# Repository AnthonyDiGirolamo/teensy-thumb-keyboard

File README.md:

# teensy-thumb-keyboard
Handheld tactile switch keyboard for Teensy 3.2 compatible boards.

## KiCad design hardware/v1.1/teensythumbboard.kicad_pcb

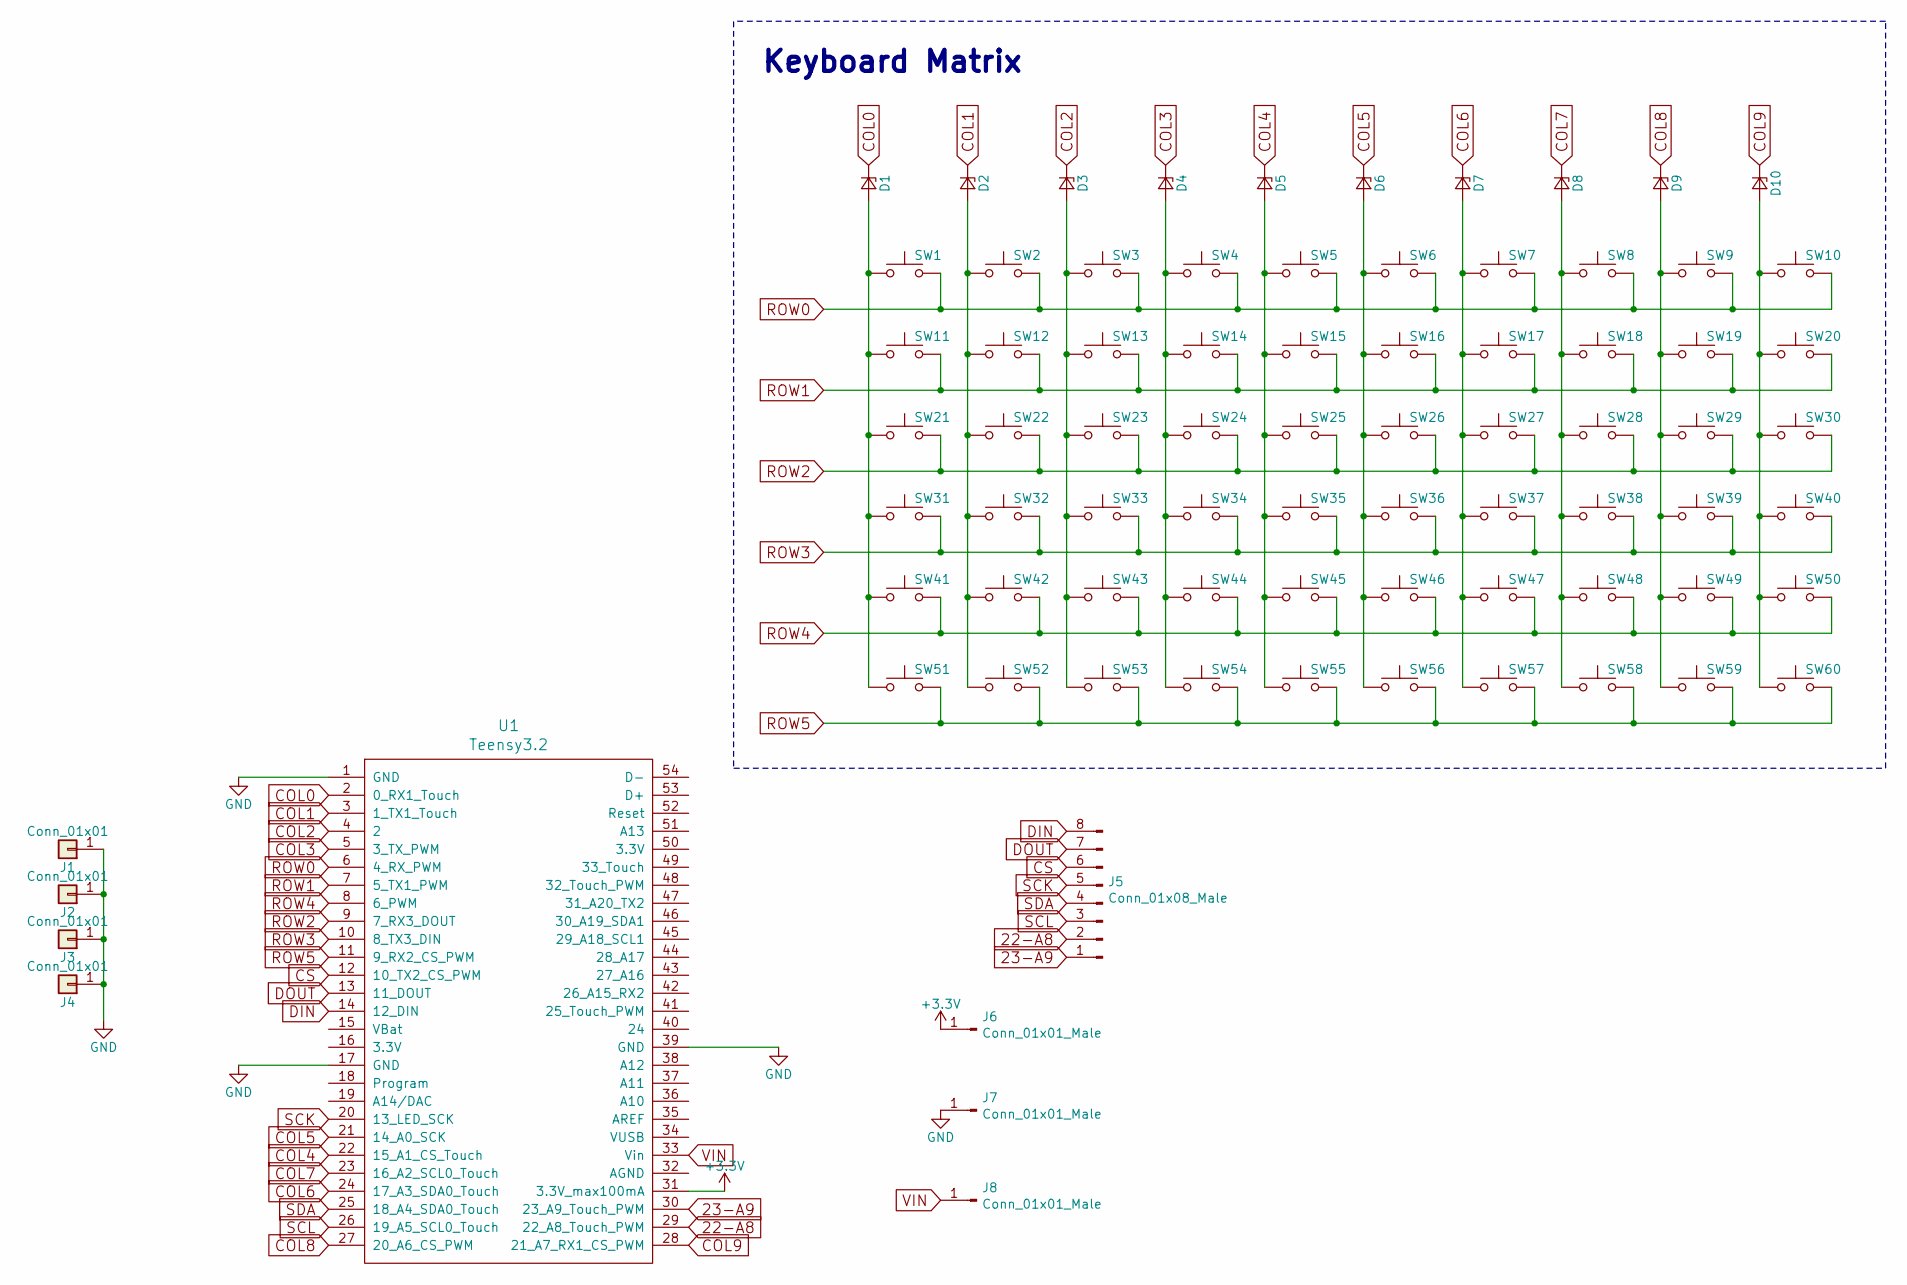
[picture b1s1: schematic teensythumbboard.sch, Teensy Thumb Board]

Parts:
D1, D2, D3, D4, D5, D6, D7, D8, D9, D10: D_Zener_Small; D_T-1_P5.08mm_Horizontal
J1, J2, J3, J4: Conn_01x01; 2.5MountingHole
J5: Conn_01x08_Male; PinSocket_1x08_P2.54mm_Vertical
J6, J7, J8: Conn_01x01_Male; PinHeader_1x01_P2.54mm_Vertical
SW1, SW2, SW3, SW4, SW5, SW6, SW7, SW8, SW9, SW10, SW11, SW12, SW13, SW14, SW15, SW16, SW17, SW18, SW19, SW20, SW21, SW22, SW23, SW24, SW25, SW26, SW27, SW28, SW29, SW30, SW31, SW32, SW33, SW34, SW35, SW36, SW37, SW38, SW39, SW40, SW41, SW42, SW43, SW44, SW45, SW46, SW47, SW48, SW49, SW50, SW51, SW52, SW53, SW54, SW55, SW56, SW57, SW58, SW59, SW60: SW_Push; SW_PUSH_6mm
U1: Teensy3.2; Teensy32_InnerProto

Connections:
22-A8: J5.2, U1.29 (22_A8_Touch_PWM)
23-A9: J5.1, U1.30 (23_A9_Touch_PWM)
+3V3: J6.1, U1.31 (3.3V_max100mA)
COL0: D1.1 (K), U1.2 (0_RX1_Touch)
COL1: D2.1 (K), U1.3 (1_TX1_Touch)
COL2: D3.1 (K), U1.4 (2)
COL3: D4.1 (K), U1.5 (3_TX_PWM)
COL4: D5.1 (K), U1.22 (15_A1_CS_Touch)
COL5: D6.1 (K), U1.21 (14_A0_SCK)
COL6: D7.1 (K), U1.24 (17_A3_SDA0_Touch)
COL7: D8.1 (K), U1.23 (16_A2_SCL0_Touch)
COL8: D9.1 (K), U1.27 (20_A6_CS_PWM)
COL9: D10.1 (K), U1.28 (21_A7_RX1_CS_PWM)
CS: J5.6, U1.12 (10_TX2_CS_PWM)
DIN: J5.8, U1.14 (12_DIN)
DOUT: J5.7, U1.13 (11_DOUT)
GND: J1.1, J2.1, J3.1, J4.1, J7.1, U1.1 (GND), U1.17 (GND), U1.39 (GND)
unnamed: D1.2 (A), SW1.1, SW11.1, SW21.1, SW31.1, SW41.1, SW51.1
unnamed: D2.2 (A), SW2.1, SW12.1, SW22.1, SW32.1, SW42.1, SW52.1
unnamed: D3.2 (A), SW3.1, SW13.1, SW23.1, SW33.1, SW43.1, SW53.1
unnamed: D4.2 (A), SW4.1, SW14.1, SW24.1, SW34.1, SW44.1, SW54.1
unnamed: D5.2 (A), SW5.1, SW15.1, SW25.1, SW35.1, SW45.1, SW55.1
unnamed: D6.2 (A), SW6.1, SW16.1, SW26.1, SW36.1, SW46.1, SW56.1
unnamed: D7.2 (A), SW7.1, SW17.1, SW27.1, SW37.1, SW47.1, SW57.1
unnamed: D8.2 (A), SW8.1, SW18.1, SW28.1, SW38.1, SW48.1, SW58.1
unnamed: D9.2 (A), SW9.1, SW19.1, SW29.1, SW39.1, SW49.1, SW59.1
unnamed: D10.2 (A), SW10.1, SW20.1, SW30.1, SW40.1, SW50.1, SW60.1
ROW0: SW1.2, SW2.2, SW3.2, SW4.2, SW5.2, SW6.2, SW7.2, SW8.2, SW9.2, SW10.2, U1.6 (4_RX_PWM)
ROW1: SW11.2, SW12.2, SW13.2, SW14.2, SW15.2, SW16.2, SW17.2, SW18.2, SW19.2, SW20.2, U1.7 (5_TX1_PWM)
ROW2: SW21.2, SW22.2, SW23.2, SW24.2, SW25.2, SW26.2, SW27.2, SW28.2, SW29.2, SW30.2, U1.9 (7_RX3_DOUT)
ROW3: SW31.2, SW32.2, SW33.2, SW34.2, SW35.2, SW36.2, SW37.2, SW38.2, SW39.2, SW40.2, U1.10 (8_TX3_DIN)
ROW4: SW41.2, SW42.2, SW43.2, SW44.2, SW45.2, SW46.2, SW47.2, SW48.2, SW49.2, SW50.2, U1.8 (6_PWM)
ROW5: SW51.2, SW52.2, SW53.2, SW54.2, SW55.2, SW56.2, SW57.2, SW58.2, SW59.2, SW60.2, U1.11 (9_RX2_CS_PWM)
SCK: J5.5, U1.20 (13_LED_SCK)
SCL: J5.3, U1.26 (19_A5_SCL0_Touch)
SDA: J5.4, U1.25 (18_A4_SDA0_Touch)
VIN: J8.1, U1.33 (Vin)

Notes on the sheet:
Keyboard Matrix

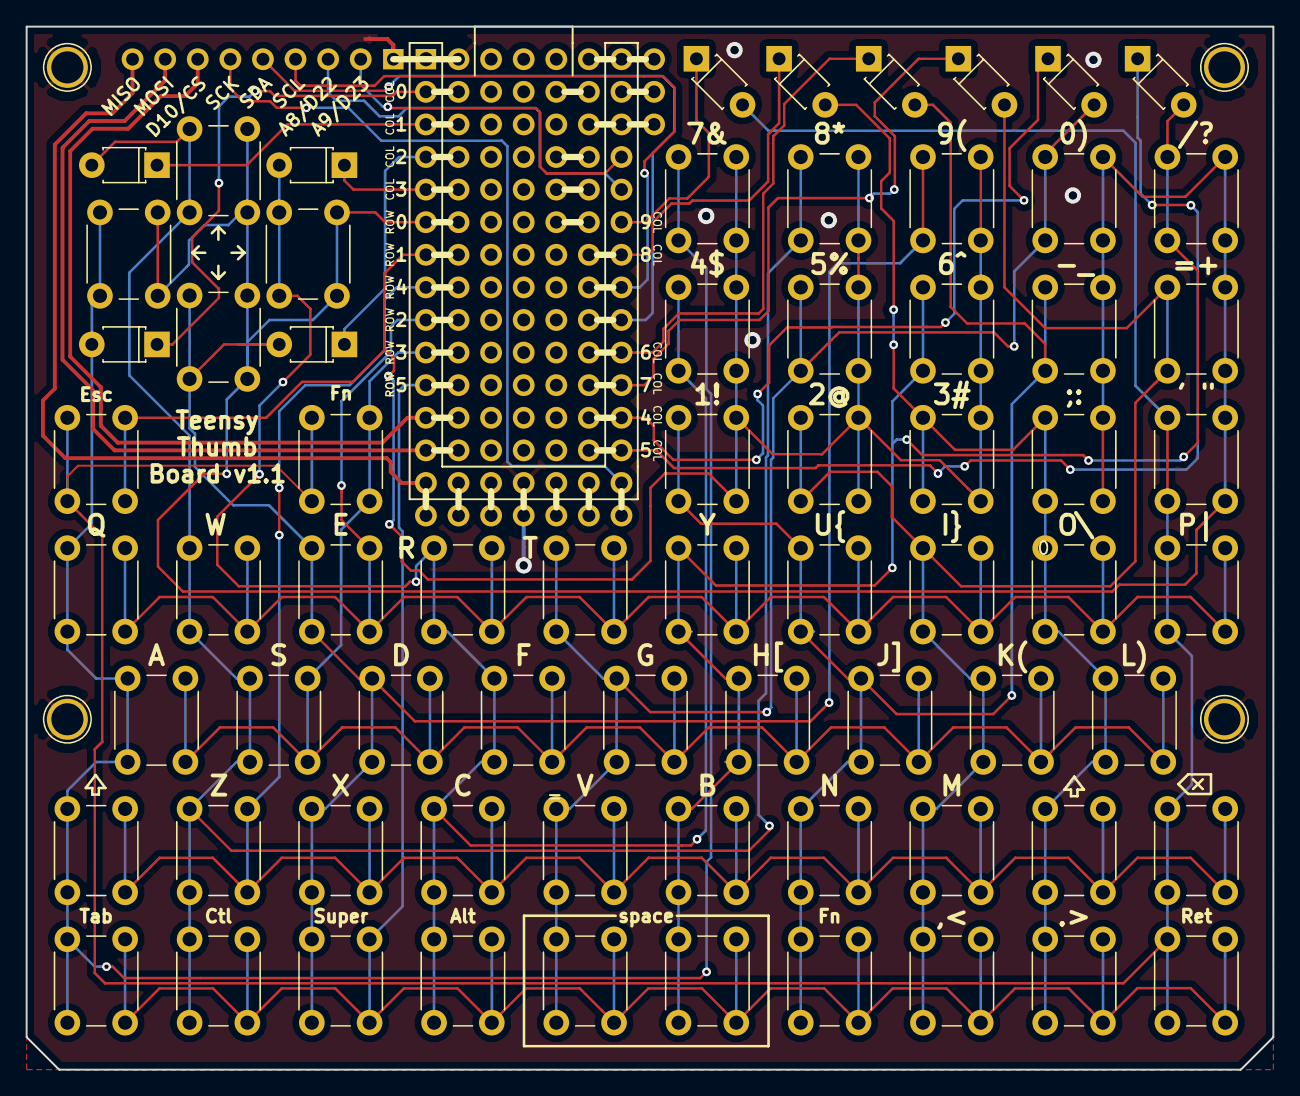
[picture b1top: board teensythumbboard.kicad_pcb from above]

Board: 2 copper layers, 97.2 x 81.3 mm, 77 parts (0 on the bottom side), 35 nets.

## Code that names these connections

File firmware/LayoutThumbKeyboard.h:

#ifndef LAYOUTTHUMBKEYBOARD_H
#define LAYOUTTHUMBKEYBOARD_H

#include <Arduino.h>
#include "LayoutCommon.h"

#define NUM_ROWS 6
#define NUM_COLS 10

// USB Facing Up
// Row Pins
#define ROW0 4
#define ROW1 5
#define ROW2 7
#define ROW3 8
#define ROW4 6
#define ROW5 9
// Column Pins
#define COL0 0
#define COL1 1
#define COL2 2
#define COL3 3
#define COL4 15
#define COL5 14
#define COL6 17
#define COL7 16
#define COL8 20
#define COL9 21

// // USB Facing Down
// // Row Pins
// #define ROW0 18
// #define ROW1 19
// #define ROW2 21
// #define ROW3 22
// #define ROW4 20
// #define ROW5 23
// // Column Pins
// #define COL0 14
// #define COL1 15
// #define COL2 16
// #define COL3 17
// #define COL4 1
// #define COL5 0
// #define COL6 3
// #define COL7 2
// #define COL8 6
// #define COL9 7

const uint8_t row_pins[] =
  {
   ROW0,
   ROW1,
   ROW2,
   ROW3,
   ROW4,
   ROW5,
  };

const uint8_t col_pins[] =
  {
   COL0,
   COL1,
   COL2,
   COL3,
   COL4,
   COL5,
   COL6,
   COL7,
   COL8,
   COL9,
  };

const char ascii_key_matrix[3][NUM_ROWS][NUM_COLS] =
  {
   // Base Layer
   {
    {ASCII_LEFT,  ASCII_UP,   ASCII_DOWN,  ASCII_RIGHT, '0', '/', '-',      '=', ';',         39}, // 39 = single quote
    {'7',         '8',        '9',         '4',         '5', '6', '1',      '2', '3',         ASCII_ESC},
    {'q',         'w',        'e',         'r',         't', 'y', 'u',      'i', 'o',         'p'},
    {'a',         's',        'd',         'f',         'g', 'h', 'j',      'k', 'l',         ASCII_FN},
    {ASCII_SHIFT, 'z',        'x',         'c',         'v', 'b', 'n',      'm', ASCII_SHIFT, '\b'},
    {'\t',        ASCII_CTRL, ASCII_SUPER, ASCII_ALT,   ' ', ' ', ASCII_FN, ',', '.',         '\n'},
   },
   // Shift Layer
   {
    {0,   0,   0,   0,   ')', '?', '_', '+', ':',  '"'},
    {'&', '*', '(', '$', '%', '^', '!', '@', '#',  0},
    {'Q', 'W', 'E', 'R', 'T', 'Y', 'U', 'I', 'O',  'P'},
    {'A', 'S', 'D', 'F', 'G', 'H', 'J', 'K', 'L',  0},
    {0,   'Z', 'X', 'C', 'V', 'B', 'N', 'M', 0,    0},
    {0,   0,   0,   0,   0,   0,   0,   '<', '>',  0},
   },
   // Fn Layer
   {
    {ASCII_MOUSE_LEFT,     ASCII_MOUSE_UP, ASCII_MOUSE_DOWN, ASCII_MOUSE_RIGHT,      0, 0,                    ASCII_MOUSE_BTN2, ASCII_MOUSE_BTN3, 0,    96},
    {ASCII_MOUSE_WHEEL_UP, 0,              0,                ASCII_MOUSE_WHEEL_DOWN, 0, ASCII_MOUSE_BTN1,     0,                0,                0,    126},
    {0,                    0,              0,                0,                      0, 0,                    '{',              '}',              '\\', '|'},
    {0,                    0,              0,                0,                      0, '[',                  ']',              '(',              ')',  0},
    {0,                    0,              0,                0,                      0, 0,                    0,                0,                0,    0},
    {0,                    0,              0,                0,                      0, ASCII_FN_LOCK_TOGGLE, 0,                0,                0,    0},
   },
  };


// for all keycodes see:
// ~/apps/arduino-1.8.5/hardware/teensy/avr/cores/teensy3/keylayouts.h
// https://www.pjrc.com/teensy/td_keyboard.html
const uint16_t usb_key_matrix[NUM_ROWS][NUM_COLS] =
  // Base Layer
  {
   {KEY_LEFT,          KEY_UP,           KEY_DOWN,        KEY_RIGHT,       KEY_0,     KEY_SLASH, KEY_MINUS, KEY_EQUAL, KEY_SEMICOLON,     KEY_QUOTE},
   {KEY_7,             KEY_8,            KEY_9,           KEY_4,           KEY_5,     KEY_6,     KEY_1,     KEY_2,     KEY_3,             KEY_ESC},
   {KEY_Q,             KEY_W,            KEY_E,           KEY_R,           KEY_T,     KEY_Y,     KEY_U,     KEY_I,     KEY_O,             KEY_P},
   {KEY_A,             KEY_S,            KEY_D,           KEY_F,           KEY_G,     KEY_H,     KEY_J,     KEY_K,     KEY_L,             ASCII_FN},
   {MODIFIERKEY_SHIFT, KEY_Z,            KEY_X,           KEY_C,           KEY_V,     KEY_B,     KEY_N,     KEY_M,     MODIFIERKEY_SHIFT, KEY_BACKSPACE},
   {KEY_TAB,           MODIFIERKEY_CTRL, MODIFIERKEY_GUI, MODIFIERKEY_ALT, KEY_SPACE, KEY_SPACE, ASCII_FN,  KEY_COMMA, KEY_PERIOD,        KEY_ENTER},
  };

#endif

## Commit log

2018-11-11 Add v1.0 kicad project
2018-11-11 Add v1.1 kicad project
2018-11-11 Update README, add images and stls
2018-11-20 Add example firmware
2018-11-30 slow down mouse speed a bit
2018-11-30 add photo of tested v1.1
2018-11-30 Add some details about the firmware
2018-12-05 add key label svg
2018-12-14 update Support2 to be rotated correctly, add more photos
2018-12-14 update readme and photos
2019-03-03 Add LCDBezel-TouchVersion.stl and Support1_v2.stl (adds additional screen pcb clearance).
2019-07-29 Add compilation instructions for Windows machines
2019-07-29 Add pre-compiled firmware hex files
2020-02-24 Add link to the i2c-thumb-keyboard repo
